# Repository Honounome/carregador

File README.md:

# Carregador
Uma fonte com tensão variável.

## Intruções para o trabalho
O objetivo do trabalho é criar uma fonte que possa carregar um aparelho celular, sendo possível controlar sua saída, a qual varia de 3V até 12V.

## Componentes e preços
Quantidade | Componentes | Preço
---------- | ----------- | -----
1 | Capacitor 820uf 35V | R$ 3,23
1 | LED vermelho 5mm | R$ 0,30
1 | Diodo Zenner 13V | R$ 0,25
1 | Transistor NPN | R$ 0,50
1 | Potenciômetro 5K ohms | R$ 2,25
1 | Resistor 1k| R$ 0,05
1 | Resistor 2.7K | R$ 0,05
1 | Resistor 2.2k | R$ 0,05

## Componentes
* Transformador: Reduz a tensão média de 127V para 18.1V;
* Ponte de diodo: possibilita que a corrente variável da tomada fique contínua;
* Capacitor: armazena e descarrega carga durante o funcionamento do circuito, diminuindo o ripple do circuito;
* Diodo Zener: regula a tensão do circuito para que o ripple seja cortado;
* Resistores: reduzem tensão, impedindo que o valor da corrente ultrapasse os limites dos componentes do circuito (fazem isso ao dissipar a potência através de calor);
* Potenciometro: componente de resistência variável que permite a variação entre 3V e 12V nas saídas da fonte;
* Transistor: utilizado para amplificar a corrente que passa para as saídas da fonte.

## Cálculos
Por conta da ponte de diodos, a voltagem disponível ao sistema diminui de 24V para algo próximo a 22,6V, pois os diodos em série consomem aproximadamente 1,4V.

Para o cálculo da capacitância mínima que precisamos para alcançar os 10% de ripple usamos a fórmula abaixo:

$$Ripple = \dfrac{Vpico}{2f \times C \times R}$$

Isolando a capacitância:

$$C = \dfrac{Vpico}{Ripple \times 2f \times R}$$

Queremos um ripple de 10%, ou seja, $\dfrac{Ripple}{Vpico} = 0,1$, logo $\dfrac{Vpico}{Ripple} = 10$. A resistência equivalente "R" do sistema é em média 205,94Ω. A frequência inicial era de 60Hz mas por causa da ponte de diodos conseguimos utilizar a corrente que seria "negativa" e efetivamente dobramos a frequência, por isso multiplicamos a frequência "f" por 2 na fórmula.

$$C = \dfrac{10}{120 \times 205,94} \approx 0,00040465$$

Assim, a capacitância mínima necessária é de 404,65µF. No projeto utilizamos um capacitor de 820µF pois o valor encontrado é apenas o mínimo, ficamos então com um ripple mais próximo a 5%.

## Falstad

[Circuito no Falstad](https://tinyurl.com/29td5cmg)

## Imagem da fonte / protoboard

## Imagem da PCB

## Imagens do CAD

## Vídeo do Projeto
[Vídeo do Projeto](https://www.youtube.com/watch?v=1EafWx9WRCc)

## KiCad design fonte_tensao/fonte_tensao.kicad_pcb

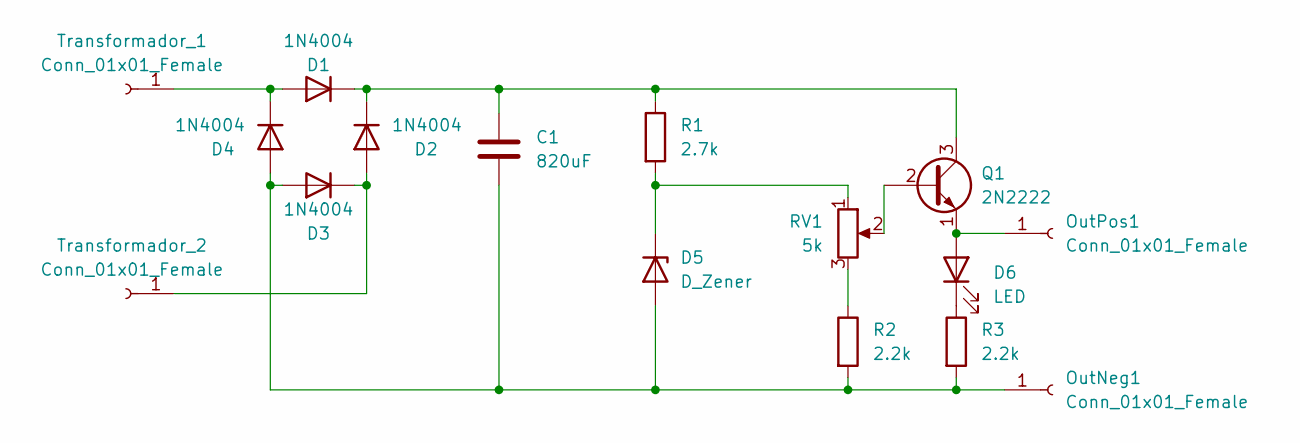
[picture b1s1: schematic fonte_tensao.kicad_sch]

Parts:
C1: 820uF; C_Radial_D6.3mm_H11.0mm_P2.50mm
D1, D2, D3, D4: 1N4004; D_DO-41_SOD81_P10.16mm_Horizontal
D5: D_Zener; D_DO-35_SOD27_P7.62mm_Horizontal
D6: LED; LED_D5.0mm_Clear
OutNeg1: Conn_01x01_Female; Pin_D1.0mm_L10.0mm
OutPos1: Conn_01x01_Female; Pin_D1.0mm_L10.0mm
Q1: 2N2222; TO-39-3
R1: 2.7k; R_Axial_DIN0411_L9.9mm_D3.6mm_P15.24mm_Horizontal
R2, R3: 2.2k; R_Axial_DIN0309_L9.0mm_D3.2mm_P15.24mm_Horizontal
RV1: 5k; Potentiometer_Omeg_PC16BU_Vertical
Transformador_1, Transformador_2: Conn_01x01_Female; Pin_D1.0mm_L10.0mm

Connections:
unnamed: C1.1, D1.1 (K), D2.1 (K), Q1.3 (C), R1.1
unnamed: C1.2, D3.2 (A), D4.2 (A), D5.2 (A), OutNeg1.1, R2.2, R3.2
unnamed: D1.2 (A), D4.1 (K), Transformador_1.1
unnamed: D2.2 (A), D3.1 (K), Transformador_2.1
unnamed: D5.1 (K), R1.2, RV1.1
unnamed: D6.1 (K), R3.1
unnamed: D6.2 (A), OutPos1.1, Q1.1 (E)
unnamed: Q1.2 (B), RV1.2
unnamed: R2.1, RV1.3

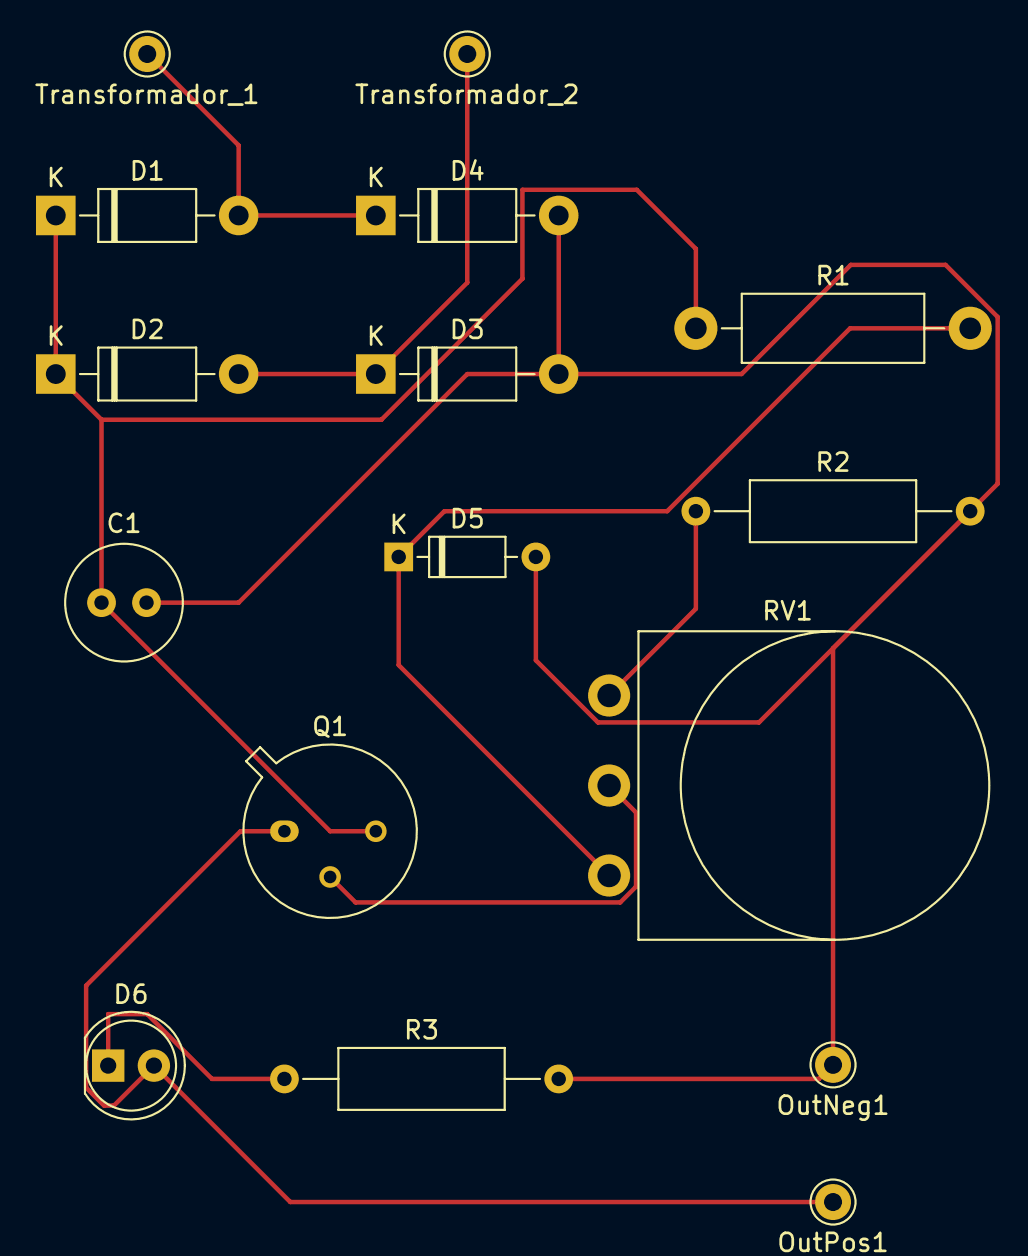
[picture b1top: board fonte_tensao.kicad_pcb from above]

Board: 2 copper layers, 16 parts (0 on the bottom side), 9 nets.

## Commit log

2023-07-10 Create qualquer coisa
2023-07-11 calculos adicionados
